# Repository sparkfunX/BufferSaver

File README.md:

SparkX SPI Buffer Saver
========================================

[*SPI Buffer Saver (SPX-14973)*](https://www.sparkfun.com/products/14973)

The SPI Buffer Saver increases the speed at which you can refresh SPI data without having to modify the Arduino core libraries. It works by rerouting the MOSI channel onto the MISO channel when the chip select pin is active using a tri-state buffer.
The same method can be used to switch other signals so take a peek at the schematic and try it out yourself!

SparkFun labored with love to create this code. Feel like supporting open source hardware? 
Buy a [board](https://www.sparkfun.com/products/14973) from SparkFun!

Repository Contents
-------------------

* **/Documents** - Datasheets
* **/Hardware** - Eagle design files (.brd, .sch)

Library
--------------
* **[Arduino Library](https://github.com/sparkfun/SparkFun_LPS25HB_Arduino_Library)** - Library for reading pressure and changing sensor settings

License Information
-------------------

This product is _**open source**_! 

If you have any questions or concerns on licensing, please contact techsupport@sparkfun.com.

Please use, reuse, and modify these files as you see fit. Please maintain attribution to SparkFun Electronics and release any derivative under the same license.

Distributed as-is; no warranty is given.

- Your friends at SparkFun.

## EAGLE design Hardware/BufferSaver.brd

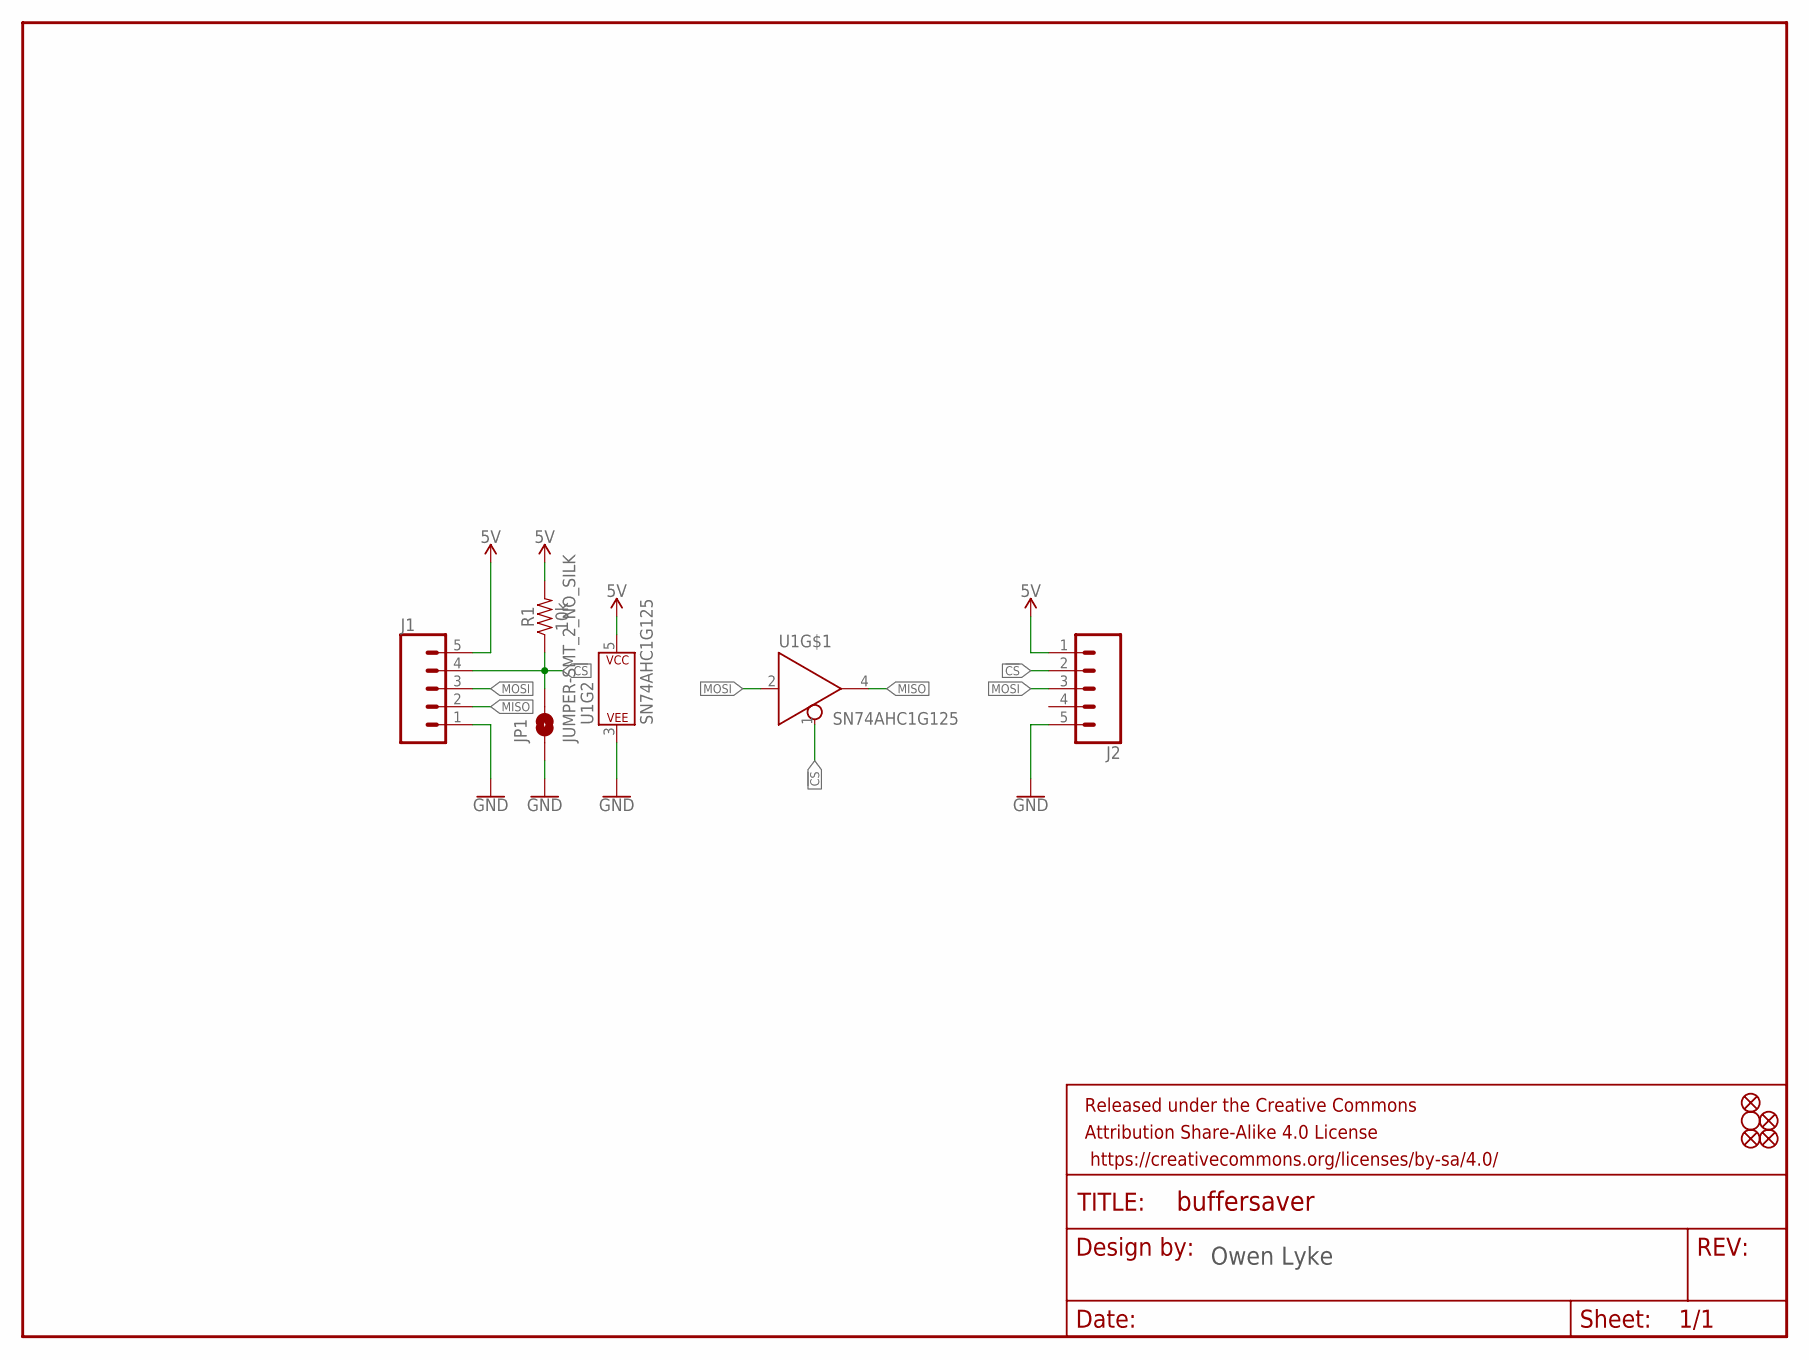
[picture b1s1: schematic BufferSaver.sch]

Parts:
FD1, FD2, FD3, FD4: FIDUCIAL1X2; FIDUCIAL-1X2
FRAME1: FRAME-LETTER; CREATIVE_COMMONS
H2: STAND-OFF
J1, J2: CONN_05NO_SILK; 1X05_NO_SILK
JP1: JUMPER-SMT_2_NO_SILK; SMT-JUMPER_2_NO_SILK
R1: 10k; 0603
U1: SN74AHC1G125; SOT23-5

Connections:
5V: J1.5, J2.1, R1.2, U1.5 (P$V+)
!CS: J1.4, J2.2, JP1.2, R1.1, U1.1 (!EN)
GND: J1.1, J2.5, JP1.1, U1.3 (P$V-)
MISO: J1.2, U1.4 (Y)
MOSI: J1.3, J2.3, U1.2 (A)

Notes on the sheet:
Owen Lyke

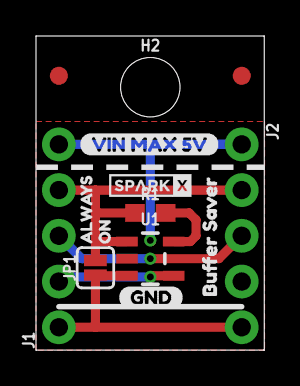
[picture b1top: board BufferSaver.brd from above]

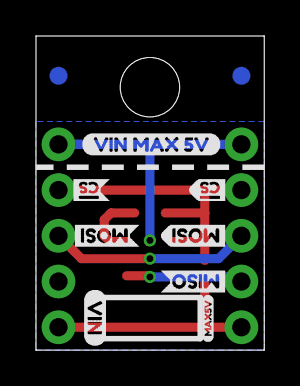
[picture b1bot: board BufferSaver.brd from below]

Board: 2 copper layers, 12.7 x 17.4 mm, 25 parts (10 on the bottom side), 5 nets.

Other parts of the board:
U$1: #CS3
U$2: #CS4
U$3, U$14: VIN_MAX_5V11
U$4: BUFFER_SAVER7
U$5: GND5
U$6: MISO2
U$7: MAX5V8
U$8: MOSI0
U$10: MOSI1
U$11: ALWAYS9
U$12: VIN6
U$13: ON10
U$34: SPARKX-LOGO2; SPARKX-TINY

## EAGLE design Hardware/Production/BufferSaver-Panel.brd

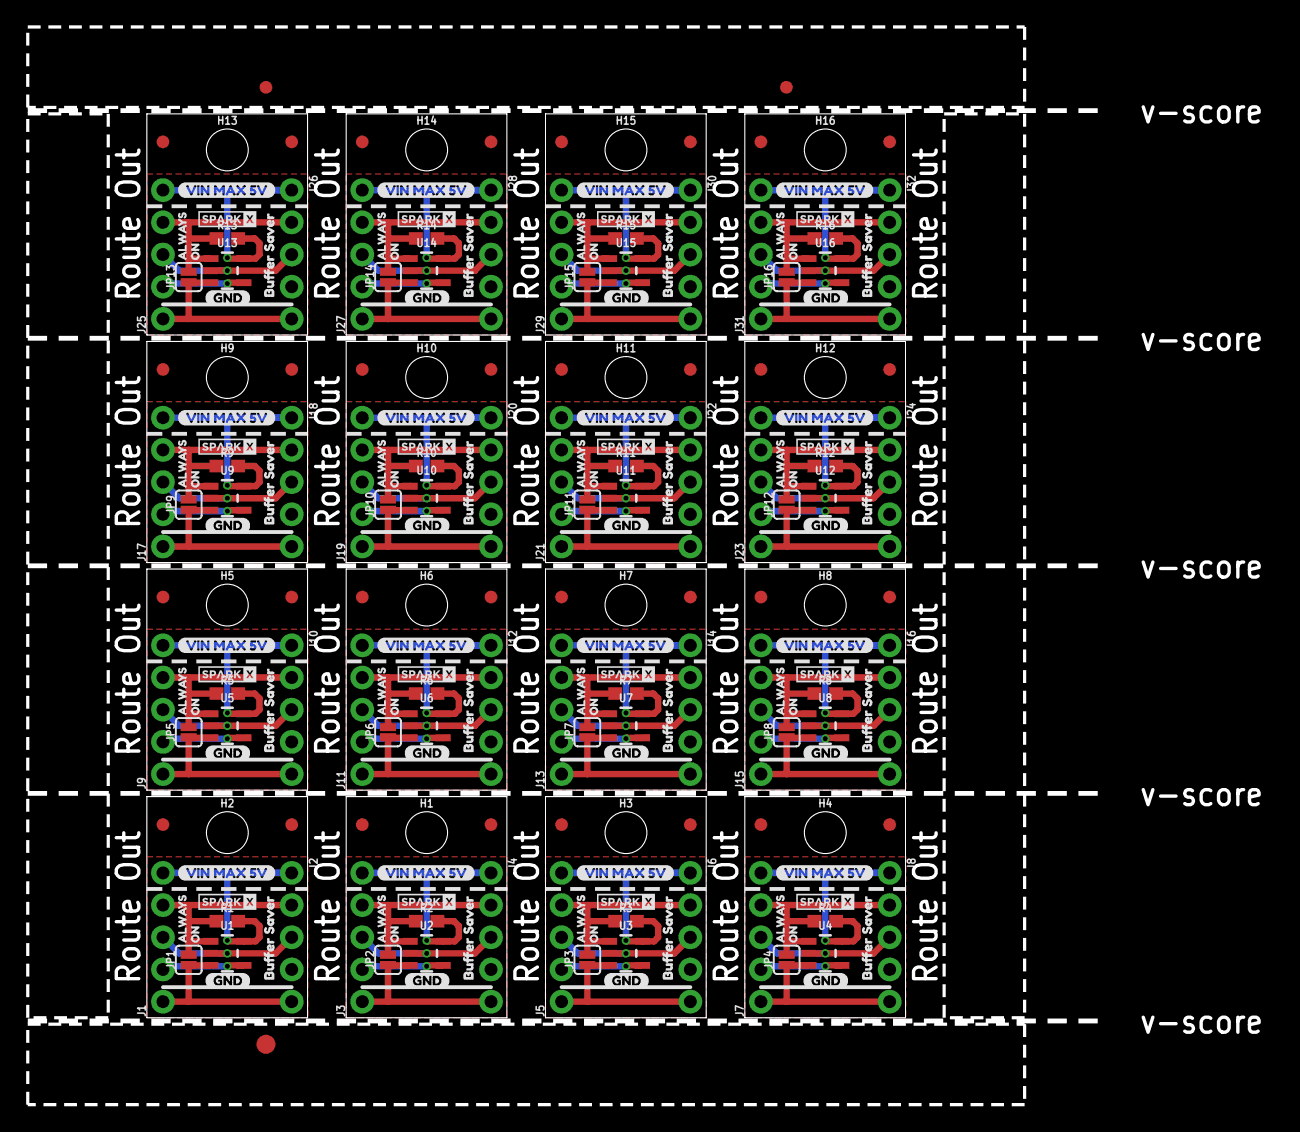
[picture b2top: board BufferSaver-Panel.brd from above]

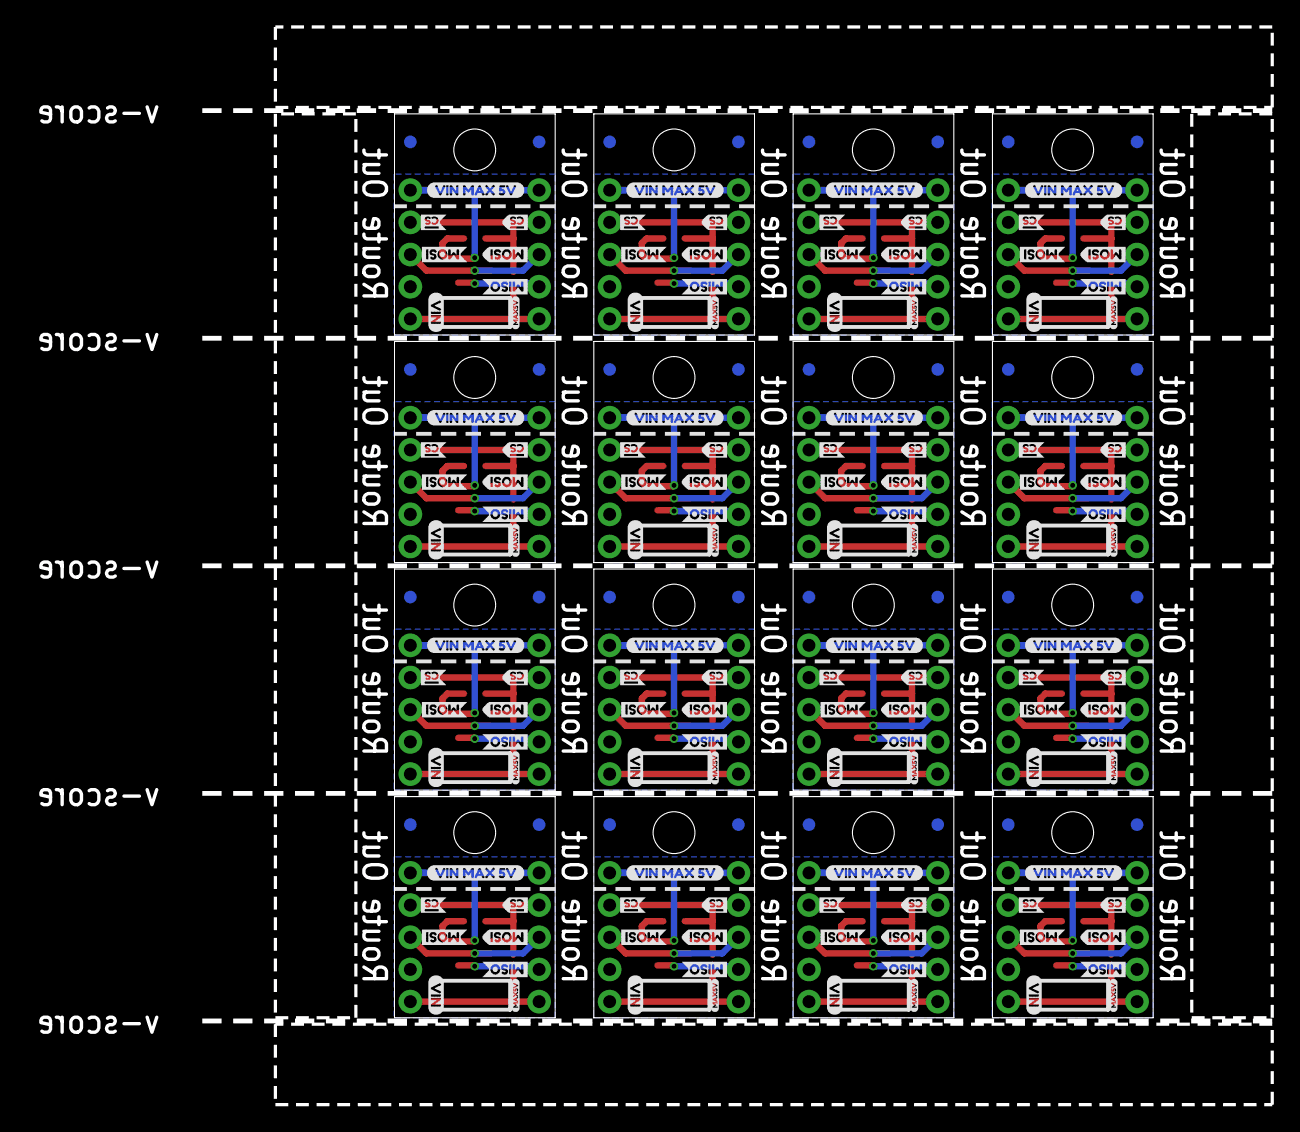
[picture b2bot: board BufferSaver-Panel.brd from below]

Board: 2 copper layers, 98.2 x 84.9 mm, 387 parts (160 on the bottom side), 80 nets.

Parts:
E$1, E$2: FIDUCIAL-1X2
E$3: FIDUCIAL-1.5X3
FD1, FD2, FD3, FD4, FD5, FD6, FD7, FD8, FD9, FD10, FD11, FD12, FD13, FD14, FD15, FD16, FD17, FD18, FD19, FD20, FD21, FD22, FD23, FD24, FD25, FD26, FD27, FD28, FD29, FD30, FD31, FD32, FD33, FD34, FD35, FD36, FD37, FD38, FD39, FD40, FD41, FD42, FD43, FD44, FD45, FD46, FD47, FD48, FD49, FD50, FD51, FD52, FD53, FD54, FD55, FD56, FD57, FD58, FD59, FD60, FD61, FD62, FD63, FD64: FIDUCIAL1X2; FIDUCIAL-1X2
H1, H2, H3, H4, H5, H6, H7, H8, H9, H10, H11, H12, H13, H14, H15, H16: STAND-OFF
J1, J2, J3, J4, J5, J6, J7, J8, J9, J10, J11, J12, J13, J14, J15, J16, J17, J18, J19, J20, J21, J22, J23, J24, J25, J26, J27, J28, J29, J30, J31, J32: 1X05_NO_SILK
JP1, JP2, JP3, JP4, JP5, JP6, JP7, JP8, JP9, JP10, JP11, JP12, JP13, JP14, JP15, JP16: JUMPER-SMT_2_NO_SILK; SMT-JUMPER_2_NO_SILK
R1, R2, R3, R4, R5, R6, R7, R8, R9, R10, R11, R12, R13, R14, R15, R16: 10k; 0603
U1, U2, U3, U4, U5, U6, U7, U8, U9, U10, U11, U12, U13, U14, U15, U16: SN74AHC1G125; SOT23-5
U$1, U$9, U$28, U$43, U$57, U$71, U$85, U$99, U$113, U$127, U$141, U$155, U$169, U$183, U$197, U$211: #CS3
U$2, U$20, U$35, U$49, U$63, U$77, U$91, U$105, U$119, U$133, U$147, U$161, U$175, U$189, U$203, U$217: #CS4
U$3, U$14, U$26, U$27, U$41, U$42, U$55, U$56, U$69, U$70, U$83, U$84, U$97, U$98, U$111, U$112, U$125, U$126, U$139, U$140, U$153, U$154, U$167, U$168, U$181, U$182, U$195, U$196, U$209, U$210, U$223, U$224: VIN_MAX_5V11
U$4, U$22, U$37, U$51, U$65, U$79, U$93, U$107, U$121, U$135, U$149, U$163, U$177, U$191, U$205, U$219: BUFFER_SAVER7
U$5, U$15, U$29, U$44, U$58, U$72, U$86, U$100, U$114, U$128, U$142, U$156, U$170, U$184, U$198, U$212: GND5
U$6, U$16, U$30, U$45, U$59, U$73, U$87, U$101, U$115, U$129, U$143, U$157, U$171, U$185, U$199, U$213: MISO2
U$7, U$23, U$38, U$52, U$66, U$80, U$94, U$108, U$122, U$136, U$150, U$164, U$178, U$192, U$206, U$220: MAX5V8
U$8, U$19, U$33, U$48, U$62, U$76, U$90, U$104, U$118, U$132, U$146, U$160, U$174, U$188, U$202, U$216: MOSI0
U$10, U$17, U$31, U$46, U$60, U$74, U$88, U$102, U$116, U$130, U$144, U$158, U$172, U$186, U$200, U$214: MOSI1
U$11, U$24, U$39, U$53, U$67, U$81, U$95, U$109, U$123, U$137, U$151, U$165, U$179, U$193, U$207, U$221: ALWAYS9
U$12, U$18, U$32, U$47, U$61, U$75, U$89, U$103, U$117, U$131, U$145, U$159, U$173, U$187, U$201, U$215: VIN6
U$13, U$25, U$40, U$54, U$68, U$82, U$96, U$110, U$124, U$138, U$152, U$166, U$180, U$194, U$208, U$222: ON10
U$21, U$34, U$36, U$50, U$64, U$78, U$92, U$106, U$120, U$134, U$148, U$162, U$176, U$190, U$204, U$218: SPARKX-LOGO2; SPARKX-TINY

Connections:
5V: J1.5, J2.1, R1.2, U1.5
5V1: J3.5, J4.1, R2.2, U2.5
5V2: J5.5, J6.1, R3.2, U3.5
5V3: J7.5, J8.1, R4.2, U4.5
5V4: J9.5, J10.1, R5.2, U5.5
5V5: J11.5, J12.1, R6.2, U6.5
5V6: J13.5, J14.1, R7.2, U7.5
5V7: J15.5, J16.1, R8.2, U8.5
5V8: J17.5, J18.1, R9.2, U9.5
5V9: J19.5, J20.1, R10.2, U10.5
5V10: J21.5, J22.1, R11.2, U11.5
5V11: J23.5, J24.1, R12.2, U12.5
5V12: J25.5, J26.1, R13.2, U13.5
5V13: J27.5, J28.1, R14.2, U14.5
5V14: J29.5, J30.1, R15.2, U15.5
5V15: J31.5, J32.1, R16.2, U16.5
!CS: J1.4, J2.2, JP1.2, R1.1, U1.1
!CS1: J3.4, J4.2, JP2.2, R2.1, U2.1
!CS2: J5.4, J6.2, JP3.2, R3.1, U3.1
!CS3: J7.4, J8.2, JP4.2, R4.1, U4.1
!CS4: J9.4, J10.2, JP5.2, R5.1, U5.1
!CS5: J11.4, J12.2, JP6.2, R6.1, U6.1
!CS6: J13.4, J14.2, JP7.2, R7.1, U7.1
!CS7: J15.4, J16.2, JP8.2, R8.1, U8.1
!CS8: J17.4, J18.2, JP9.2, R9.1, U9.1
!CS9: J19.4, J20.2, JP10.2, R10.1, U10.1
!CS10: J21.4, J22.2, JP11.2, R11.1, U11.1
!CS11: J23.4, J24.2, JP12.2, R12.1, U12.1
!CS12: J25.4, J26.2, JP13.2, R13.1, U13.1
!CS13: J27.4, J28.2, JP14.2, R14.1, U14.1
!CS14: J29.4, J30.2, JP15.2, R15.1, U15.1
!CS15: J31.4, J32.2, JP16.2, R16.1, U16.1
GND: J1.1, J2.5, JP1.1, U1.3
GND1: J3.1, J4.5, JP2.1, U2.3
GND2: J5.1, J6.5, JP3.1, U3.3
GND3: J7.1, J8.5, JP4.1, U4.3
GND4: J9.1, J10.5, JP5.1, U5.3
GND5: J11.1, J12.5, JP6.1, U6.3
GND6: J13.1, J14.5, JP7.1, U7.3
GND7: J15.1, J16.5, JP8.1, U8.3
GND8: J17.1, J18.5, JP9.1, U9.3
GND9: J19.1, J20.5, JP10.1, U10.3
GND10: J21.1, J22.5, JP11.1, U11.3
GND11: J23.1, J24.5, JP12.1, U12.3
GND12: J25.1, J26.5, JP13.1, U13.3
GND13: J27.1, J28.5, JP14.1, U14.3
GND14: J29.1, J30.5, JP15.1, U15.3
GND15: J31.1, J32.5, JP16.1, U16.3
MISO: J1.2, U1.4
MISO1: J3.2, U2.4
MISO2: J5.2, U3.4
MISO3: J7.2, U4.4
MISO4: J9.2, U5.4
MISO5: J11.2, U6.4
MISO6: J13.2, U7.4
MISO7: J15.2, U8.4
MISO8: J17.2, U9.4
MISO9: J19.2, U10.4
MISO10: J21.2, U11.4
MISO11: J23.2, U12.4
MISO12: J25.2, U13.4
MISO13: J27.2, U14.4
MISO14: J29.2, U15.4
MISO15: J31.2, U16.4
MOSI: J1.3, J2.3, U1.2
MOSI1: J3.3, J4.3, U2.2
MOSI2: J5.3, J6.3, U3.2
MOSI3: J7.3, J8.3, U4.2
MOSI4: J9.3, J10.3, U5.2
MOSI5: J11.3, J12.3, U6.2
MOSI6: J13.3, J14.3, U7.2
MOSI7: J15.3, J16.3, U8.2
MOSI8: J17.3, J18.3, U9.2
MOSI9: J19.3, J20.3, U10.2
MOSI10: J21.3, J22.3, U11.2
MOSI11: J23.3, J24.3, U12.2
MOSI12: J25.3, J26.3, U13.2
MOSI13: J27.3, J28.3, U14.2
MOSI14: J29.3, J30.3, U15.2
MOSI15: J31.3, J32.3, U16.2

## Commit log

2018-08-29 Added a second buffer to allow for multiple led strips on one SPI port!
2018-08-30 Software additions
2018-08-30 Revert "Added a second buffer to allow for multiple led strips on one SPI port!"
    This reverts commit a22a5d977a95e097da70702a3350ebab49920d41.
2018-08-30 Revert "Revert "Added a second buffer to allow for multiple led strips on one SPI port!""
    This reverts commit 93b898f1311a7606d26b6a396d53439853d3f191.
2018-08-30 Fixed buffer symbol
2018-08-31 Not sure

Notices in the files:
parts and their libraries:
SparkFun-Aesthetics: Licensing: Creative Commons ShareAlike 4.0 International - https://creativecommons.org/licenses/by-sa/4.0
SparkFun-Aesthetics: Released under the Creative Commons Attribution Share-Alike 4.0 License
SparkFun-Aesthetics: https://creativecommons.org/licenses/by-sa/4.0
